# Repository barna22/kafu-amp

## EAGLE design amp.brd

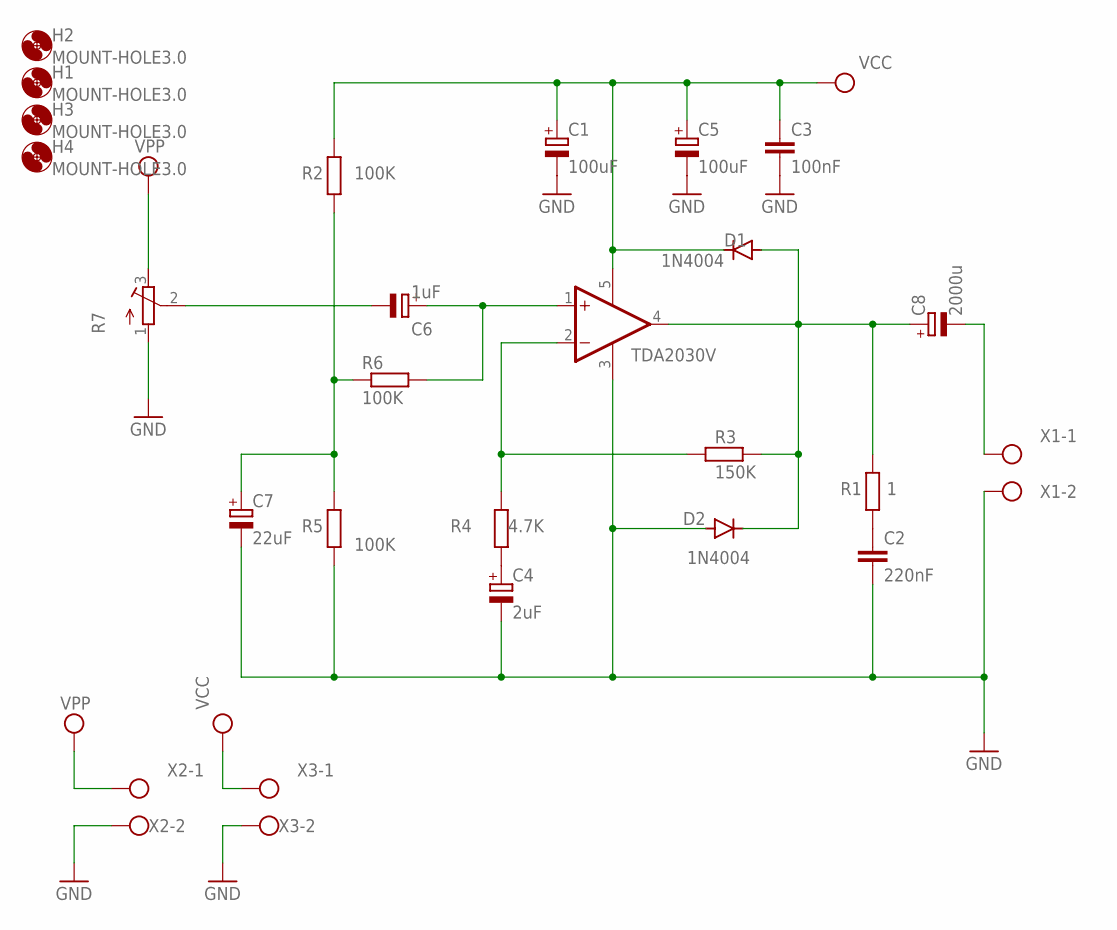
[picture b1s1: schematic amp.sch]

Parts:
C1, C5: 100uF; EB25D
C2: 220nF; C2.5-3
C3: 100nF; C2.5-3
C4: 2uF; E2,5-7
C6: 1uF; E2,5-7
C7: 22uF; E2,5-7
C8: 2000u; EB35D
D1, D2: 1N4004; DO41-10
H1, H2, H3, H4: MOUNT-HOLE3.0; 3,0
IC1: TDA2030V; CB360
R1: 1; 0207/12
R2, R5, R6: 100K; 0207/12
R3: 150K; 0207/12
R4: 4.7K; 0207/12
R7: R-TRIMM3296W; RTRIM3296W
X1, X2, X3: W237-113

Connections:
GND: C1.-, C2.2, C3.2, C4.-, C5.-, C7.-, D2.A, IC1.3 (GND), R5.1, R7.1 (A), X1.2, X2.2, X3.2
unnamed: C4.+, R4.1
unnamed: C8.-, X1.1
unnamed: C6.+, IC1.1 (+IN), R6.2
unnamed: C8.+, D1.A, D2.C, IC1.4 (OUT), R1.2, R3.2
unnamed: C2.1, R1.1
unnamed: C7.+, R2.1, R5.2, R6.1
unnamed: IC1.2 (-IN), R3.1, R4.2
unnamed: C6.-, R7.2 (S)
VCC: C1.+, C3.1, C5.+, D1.C, IC1.5 (V+), R2.2, X3.1
VPP: R7.3 (E), X2.1

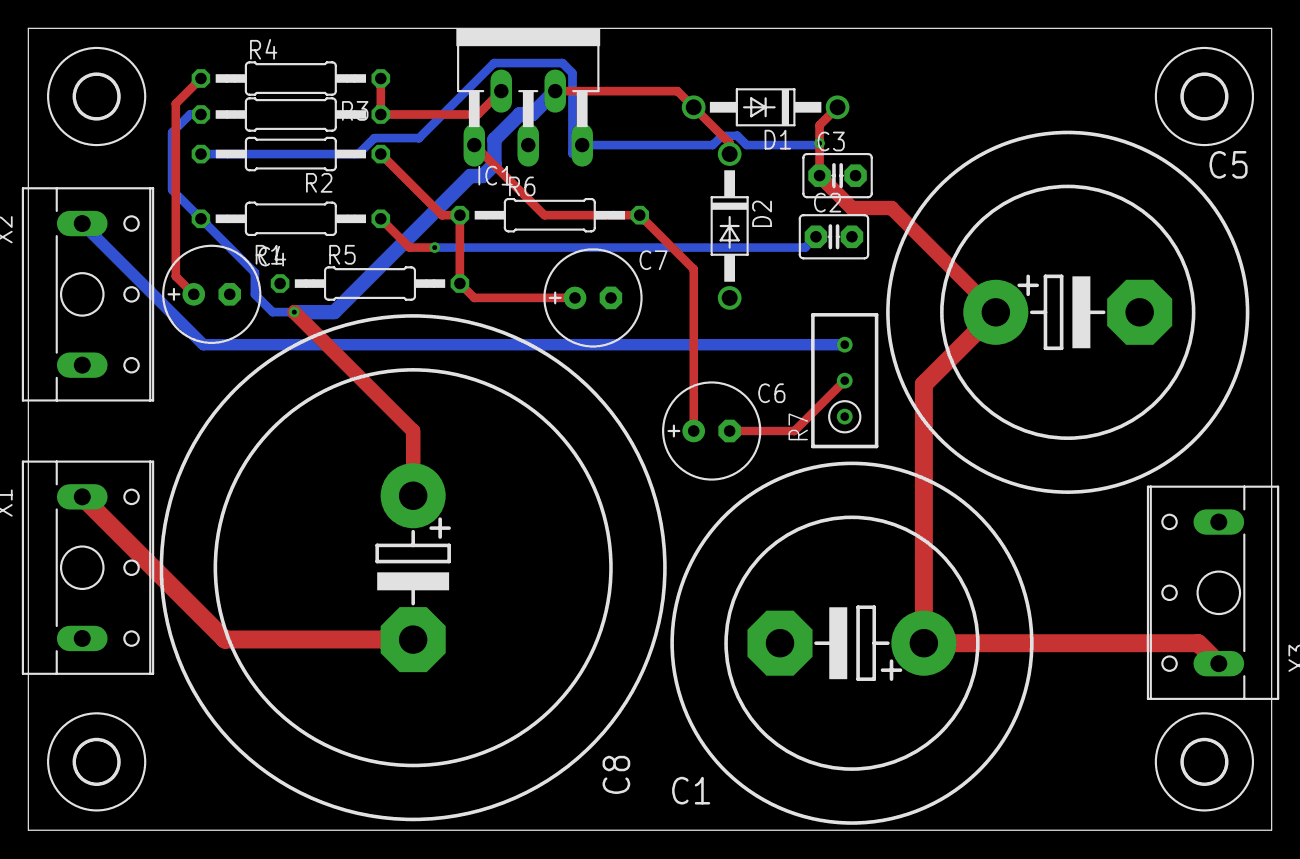
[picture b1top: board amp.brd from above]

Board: 2 copper layers, 87.8 x 56.6 mm, 25 parts (0 on the bottom side), 11 nets.

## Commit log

2019-06-27 emmegmi
2019-06-28 terv
2019-06-29 started brd
2019-06-29 Ádám igazításai
2019-07-01 some progress with brd
2019-07-01 holes added
2019-07-02 Barna .brd ver2.0
2019-07-02 final (hopefully)
2019-07-02 Final version of pcb
2019-07-02 Final version of schematic
